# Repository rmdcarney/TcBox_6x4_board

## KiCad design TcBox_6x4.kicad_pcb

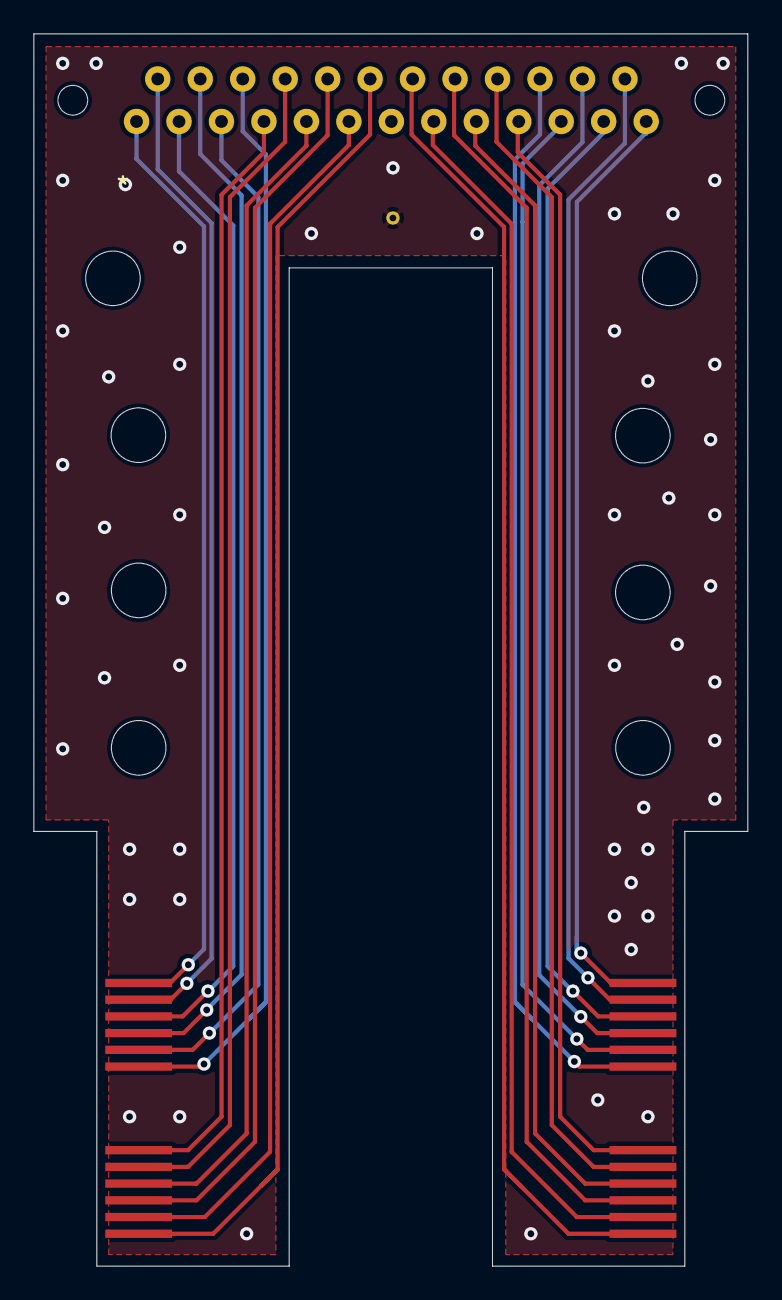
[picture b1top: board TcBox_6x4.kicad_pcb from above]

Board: 2 copper layers, 42.7 x 73.7 mm, 14 parts (1 on the bottom side), 24 nets.

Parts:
H1, H2, H3, H4, H5, H6, H7, H8: MountingHole; 4-40Clearance
J1: Conn_01x25; MDM25-SBSP
J2, J3, J4, J5: Conn_01x06_Male; WB_pad_6ch
R1: DNF (short); thruVia

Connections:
/Ch0_0: J1.1, J2.1
/Ch0_1: J1.14, J2.2
/Ch0_2: J1.2, J2.3
/Ch0_3: J1.15, J2.4
/Ch0_4: J1.3, J2.5
/Ch0_5: J1.16, J2.6
/Ch1_0: J1.4, J3.1
/Ch1_1: J1.17, J3.2
/Ch1_2: J1.5, J3.3
/Ch1_3: J1.18, J3.4
/Ch1_4: J1.6, J3.5
/Ch1_5: J1.19, J3.6
/Ch2_0: J1.20, J4.1
/Ch2_1: J1.8, J4.2
/Ch2_2: J1.21, J4.3
/Ch2_3: J1.9, J4.4
/Ch2_4: J1.22, J4.5
/Ch2_5: J1.10, J4.6
/Ch3_0: J1.23, J5.1
/Ch3_1: J1.11, J5.2
/Ch3_2: J1.24, J5.3
/Ch3_3: J1.12, J5.4
/Ch3_4: J1.25, J5.5
/Ch3_5: J1.13, J5.6

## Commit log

2024-07-30 Outline, placement, traces done.
2024-07-30 First draft. Going to branch here and try a different footprint option.
2024-08-02 Generated gerbers
2024-08-02 Pushed opdf into new folder
2024-08-02 Added a couple of other pdfs
2024-08-02 Version 1.1 - ready for fab.
